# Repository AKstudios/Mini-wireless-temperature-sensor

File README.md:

# Mini-wireless-temperature-sensor
A tiny, low power, wireless temperature and relative humidity sensor based on an RFM69 tranceiver.

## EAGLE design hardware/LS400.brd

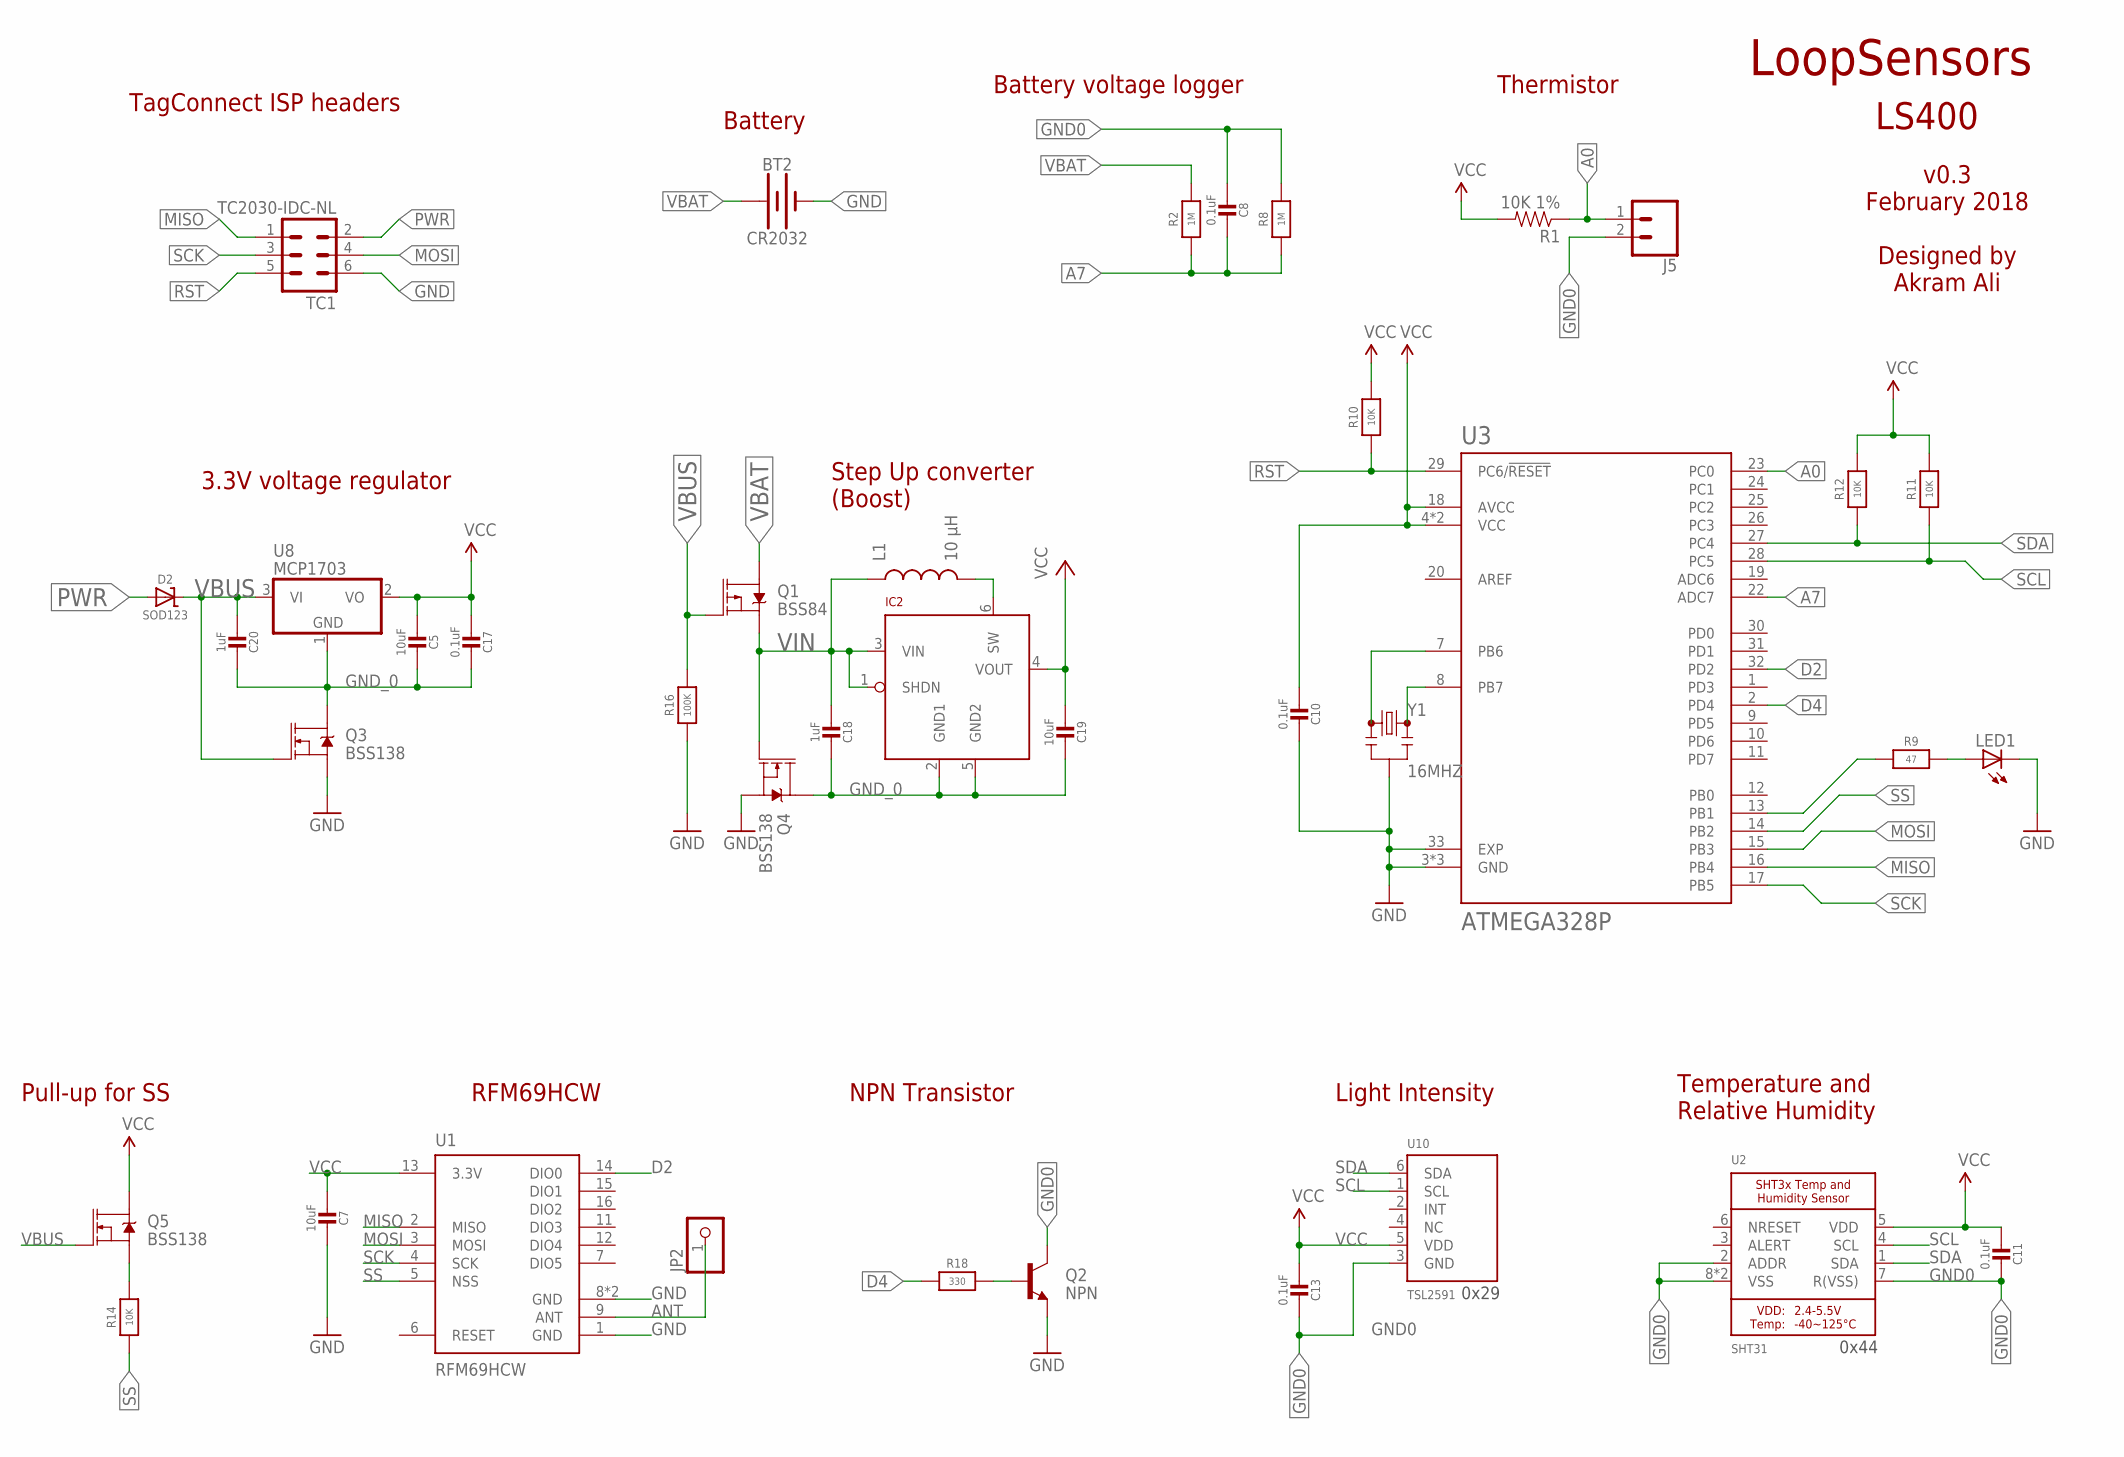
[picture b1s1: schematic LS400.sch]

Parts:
BT2: CR2032; BATTCON_20MM_4LEGS
C5, C7, C19: 10uF; MICROBUILDER__0402MP; MPN GRJ155R60J106ME11D
C8: 0.1uF; MICROBUILDER__0402MP; MPN GRM155R71C104KA88J
C10, C11, C13, C17: 0.1uF; MICROBUILDER__0402MP; MPN GRJ155R60J106ME11D
C18, C20: 1uF; MICROBUILDER__0402MP; MPN GRJ155R60J106ME11D
D2: SOD123; MICROBUILDER_SOD-123; MPN SD103AW-13-F
IC2: LTC3525; SC70
J5: CONN_02; 1X02
JP2: PINHD-1X1CB; 1X01-CLEANBIG
L1: 10 µH; 1210
LED1: LEDCHIPLED_0603; CHIPLED_0603
Q1: BSS84; SOT23-3
Q2: NPN; SOT23-3
Q3, Q4, Q5: BSS138; SOT23-3
R1: 10K 1%; 0805
R2, R8: 1M; MICROBUILDER__0402MP; MPN RC0402JR-0710KL
R9: 47; MICROBUILDER__0402MP; MPN RC0402JR-071KL
R10, R11, R12, R14: 10K; MICROBUILDER__0402MP; MPN RC0402JR-071KL
R16: 100K; MICROBUILDER__0402MP; MPN RC0402JR-071KL
R18: 330; MICROBUILDER__0402MP; MPN RC0402JR-071KL
TC1: TC2030-IDC-NL
U1: RFM69HCW; RFM69HCW-XXXS2
U2: SHT31; SHT3X; MPN SHT35-DIS-B
U3: ATMEGA328P; QFN50P500X500X100-33N
U8: MCP1703; SOT23; MPN MCP1703T-2502E/CB
U10: TSL2591; DFN6_TAOS; MPN TSL25911FN
Y1: 16MHZ; RESONATOR-SMD

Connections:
A0: J5.1, R1.1, U3.23 (PC0)
A7: C8.1, R2.1, R8.1, U3.22 (ADC7)
ANT: JP2.1, U1.9 (ANT)
D2: U1.14 (DIO0), U3.32 (PD2)
D4: R18.1, U3.2 (PD4)
GND: BT2.NEGATIVE (-), C7.1, C10.1, LED1.C, Q2.2 (E), Q3.2 (S), Q4.2 (S), R16.1, TC1.6, U1.1 (GND), U1.8 (GND), U1.10 (GND), U3.3 (GND), U3.5 (GND), U3.21 (GND), U3.33 (EXP), Y1.2
GND0: C8.2, C11.1, C13.1, J5.2, Q2.3 (C), R8.2, U2.2 (ADDR), U2.7 (R(VSS)), U2.8 (VSS), U2.THERMAL (VSS), U10.3 (GND)
GND_0: C5.1, C17.1, C18.1, C19.1, C20.1, IC2.2 (GND1), IC2.5 (GND2), Q3.3 (D), Q4.3 (D), U8.1 (GND)
MISO: TC1.1, U1.2 (MISO), U3.16 (PB4)
MOSI: TC1.4, U1.3 (MOSI), U3.15 (PB3)
unnamed: Q2.1 (B), R18.2
unnamed: R9.1, U3.13 (PB1)
unnamed: LED1.A, R9.2
unnamed: U3.8 (PB7), Y1.3
unnamed: U3.7 (PB6), Y1.1
unnamed: Q5.2 (S), R14.2
unnamed: IC2.6 (SW), L1.2
PWR: D2.A, TC1.2
RST: R10.1, TC1.5, U3.29 (PC6/!RESET)
SCK: TC1.3, U1.4 (SCK), U3.17 (PB5)
SCL: R11.1, U2.4 (SCL), U3.28 (PC5), U10.1 (SCL)
SDA: R12.1, U2.1 (SDA), U3.27 (PC4), U10.6 (SDA)
SS: R14.1, U1.5 (NSS), U3.14 (PB2)
VBAT: BT2.POSITIVE@1 (+), BT2.POSITIVE@2 (+), BT2.POSITIVE@3 (+), BT2.POSITIVE@4 (+), Q1.3 (D), R2.2
VBUS: C20.2, D2.C, Q1.1 (G), Q3.1 (G), Q5.1 (G), R16.2, U8.3 (VI)
VCC: C5.2, C7.2, C10.2, C11.2, C13.2, C17.2, C19.2, IC2.4 (VOUT), Q5.3 (D), R1.2, R10.2, R11.2, R12.2, U1.13 (3.3V), U2.5 (VDD), U3.4 (VCC), U3.6 (VCC), U3.18 (AVCC), U8.2 (VO), U10.5 (VDD)
VIN: C18.2, IC2.1 (SHDN), IC2.3 (VIN), L1.1, Q1.2 (S), Q4.1 (G)

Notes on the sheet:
3.3V voltage regulator
LoopSensors
LS400
v0.3 February 2018 Designed by Akram Ali
NPN Transistor
Battery
RFM69HCW
Light Intensity
0x29
Temperature and Relative Humidity
0x44
Step Up converter (Boost)
TagConnect ISP headers
Battery voltage logger
Pull-up for SS
Thermistor

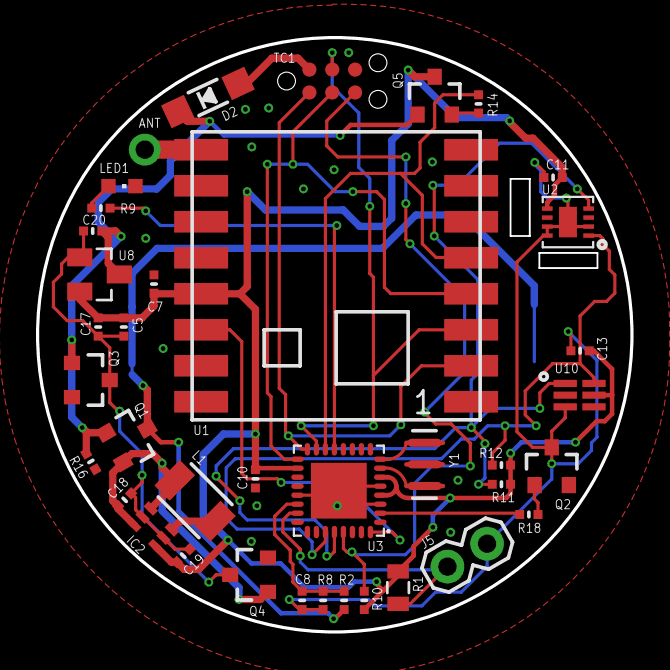
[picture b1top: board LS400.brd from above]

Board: 2 copper layers, 33.0 x 33.0 mm, 39 parts (1 on the bottom side), 27 nets.

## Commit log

2018-07-19 added OSH park render
2018-08-09 Create LICENSE

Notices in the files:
parts and their libraries:
SparkFun-FreqCtrl: Licensing: Creative Commons ShareAlike 4.0 International - https://creativecommons.org/licenses/by-sa/4.0
SparkFun: Licensing: CC v3.0 Share-Alike You are welcome to use this library for commercial purposes.
